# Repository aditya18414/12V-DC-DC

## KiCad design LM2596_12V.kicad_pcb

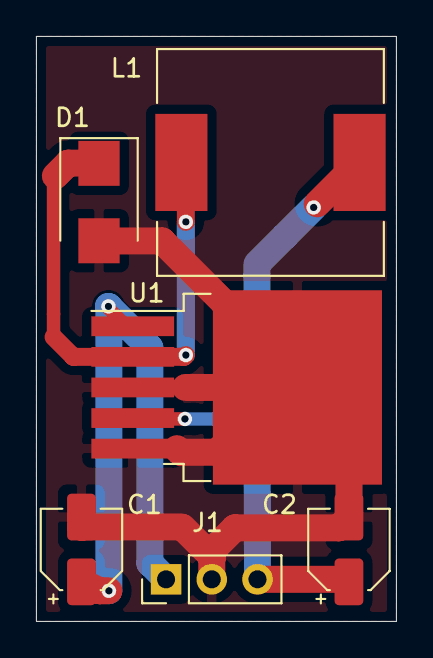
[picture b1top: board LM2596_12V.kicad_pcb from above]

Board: 2 copper layers, 20.0 x 32.5 mm, 6 parts (0 on the bottom side), 4 nets.

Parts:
C1: 470uF/50V; CP_Elec_4x4.5
C2: 220uF/35V; CP_Elec_4x4.5
D1: 1N5818; D_SMB
J1: Conn_01x03_Male; PinHeader_1x03_P2.54mm_Vertical
L1: 68uH; L_12x12mm_H4.5mm
U1: LM2596S-12; TO-263-5_TabPin3

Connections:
GND: C1.2, C2.2, D1.2, J1.2, U1.3, U1.5
unnamed: C1.1, J1.1, U1.INPUT
unnamed: C2.1, J1.3, L1.2, U1.FEDBACK
unnamed: D1.1, L1.1, U1.OUTPUT

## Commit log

2021-06-09 Create Lm2596
